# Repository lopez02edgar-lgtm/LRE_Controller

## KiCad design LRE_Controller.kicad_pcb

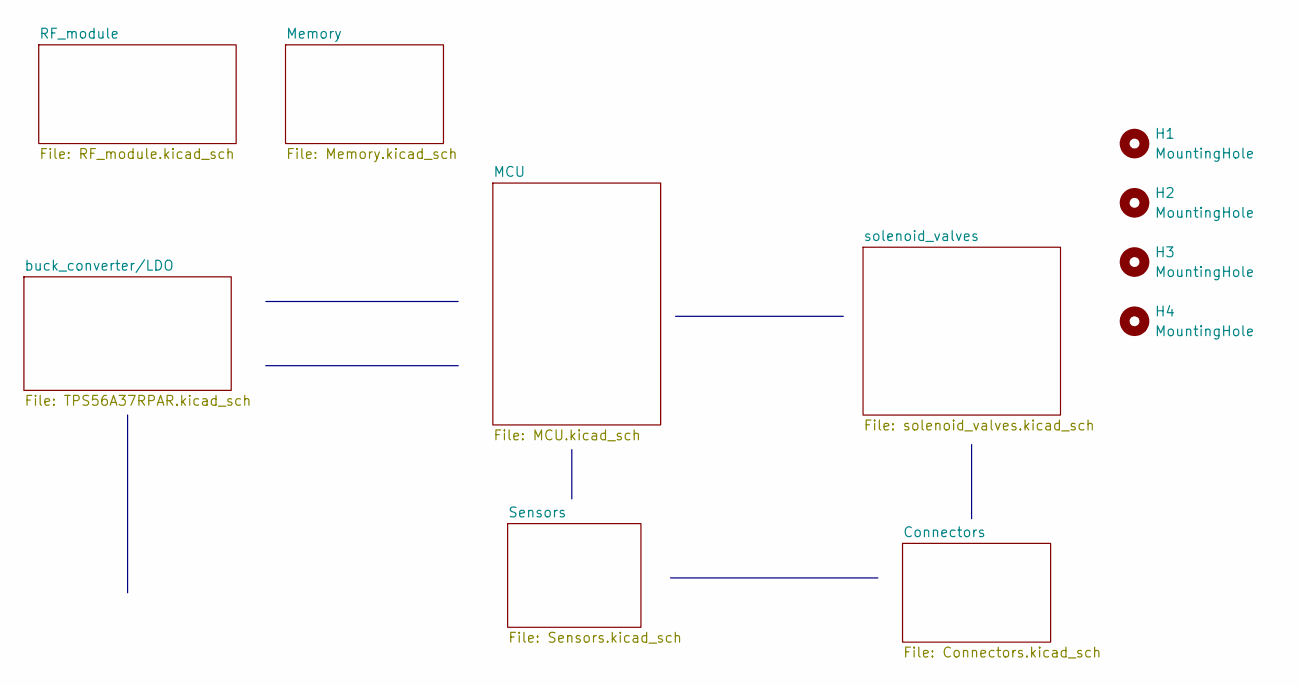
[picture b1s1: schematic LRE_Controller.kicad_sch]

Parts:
H1, H2, H3, H4: MountingHole; MountingHole_3.2mm_M3

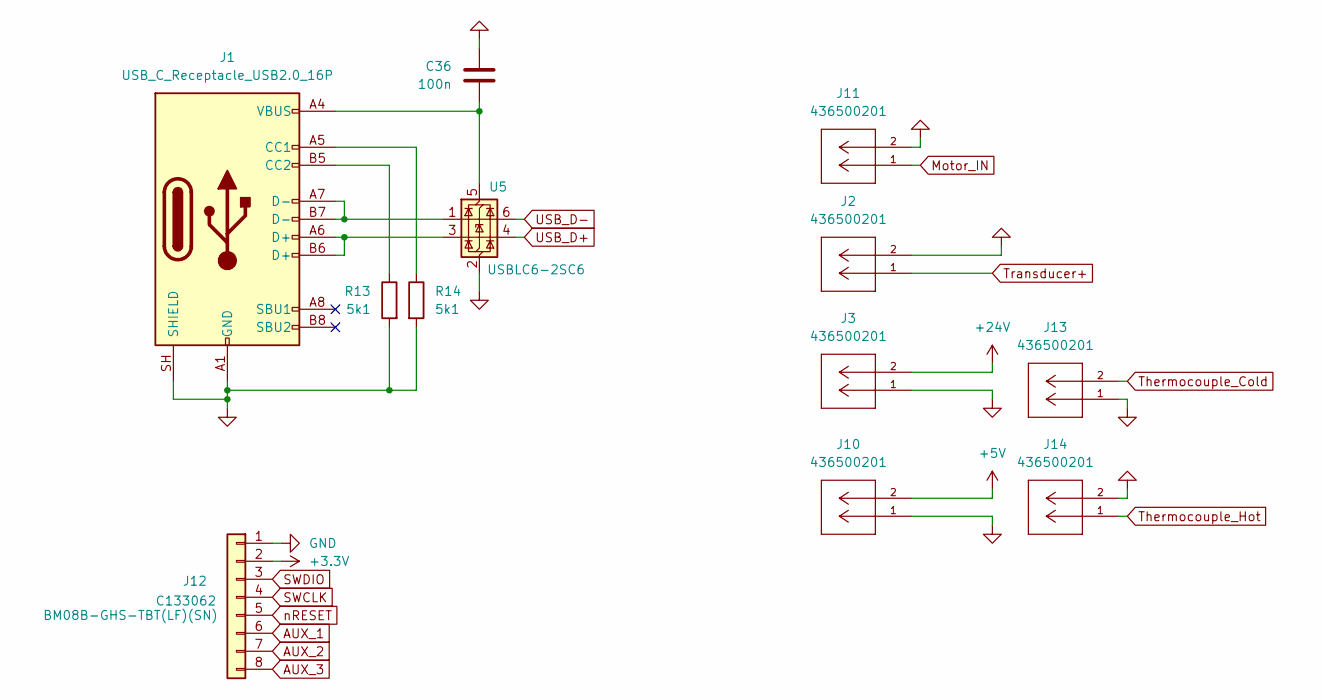
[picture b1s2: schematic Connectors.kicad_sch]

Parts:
C36: 100n; C_0402_1005Metric
J1: USB_C_Receptacle_USB2.0_16P; USB_C_Receptacle_GCT_USB4105-xx-A_16P_TopMnt_Horizontal
J2, J3, J10, J11, J13, J14: 436500201; CONN_SD-43650-001_02_MOL; MANUFACTURER_PART_NUMBER 436500201
J12: BM08B-GHS-TBT(LF)(SN); JST_GH_BM08B-GHS-TBT_1x08-1MP_P1.25mm_Vertical; LCSC C133062
R13, R14: 5k1; R_0402_1005Metric
U5: USBLC6-2SC6; SOT-23-6

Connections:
+3.3V: J12.2; also elsewhere on the board
+5V: J10.2; also elsewhere on the board
+24V: J3.2; also elsewhere on the board
ADC0 (P.T): J2.1; also elsewhere on the board
AUX_1: J12.6; also elsewhere on the board
AUX_2: J12.7; also elsewhere on the board
AUX_3: J12.8; also elsewhere on the board
GND: C36.1, J1.A1 (GND), J1.A12 (GND), J1.B1 (GND), J1.B12 (GND), J1.SH (SHIELD), J2.2, J3.1, J10.1, J11.2, J12.1, J13.1, J14.2, R13.2, R14.2, U5.2 (GND); also elsewhere on the board
Motor_IN: J11.1; also elsewhere on the board
unnamed: J1.A5 (CC1), R14.1
unnamed: J1.B5 (CC2), R13.1
unnamed: J1.A6 (D+), J1.B6 (D+), U5.3 (I/O2)
unnamed: J1.A7 (D-), J1.B7 (D-), U5.1 (I/O1)
unnamed: C36.2, J1.A4 (VBUS), J1.A9 (VBUS), J1.B4 (VBUS), J1.B9 (VBUS), U5.5 (VBUS)
SWCLK: J12.4; also elsewhere on the board
SWDIO: J12.3; also elsewhere on the board
Thermocouple_Cold: J13.2; also elsewhere on the board
Thermocouple_Hot: J14.1; also elsewhere on the board
USB_D+: U5.4 (I/O2); also elsewhere on the board
USB_D-: U5.6 (I/O1); also elsewhere on the board
nRESET: J12.5; also elsewhere on the board

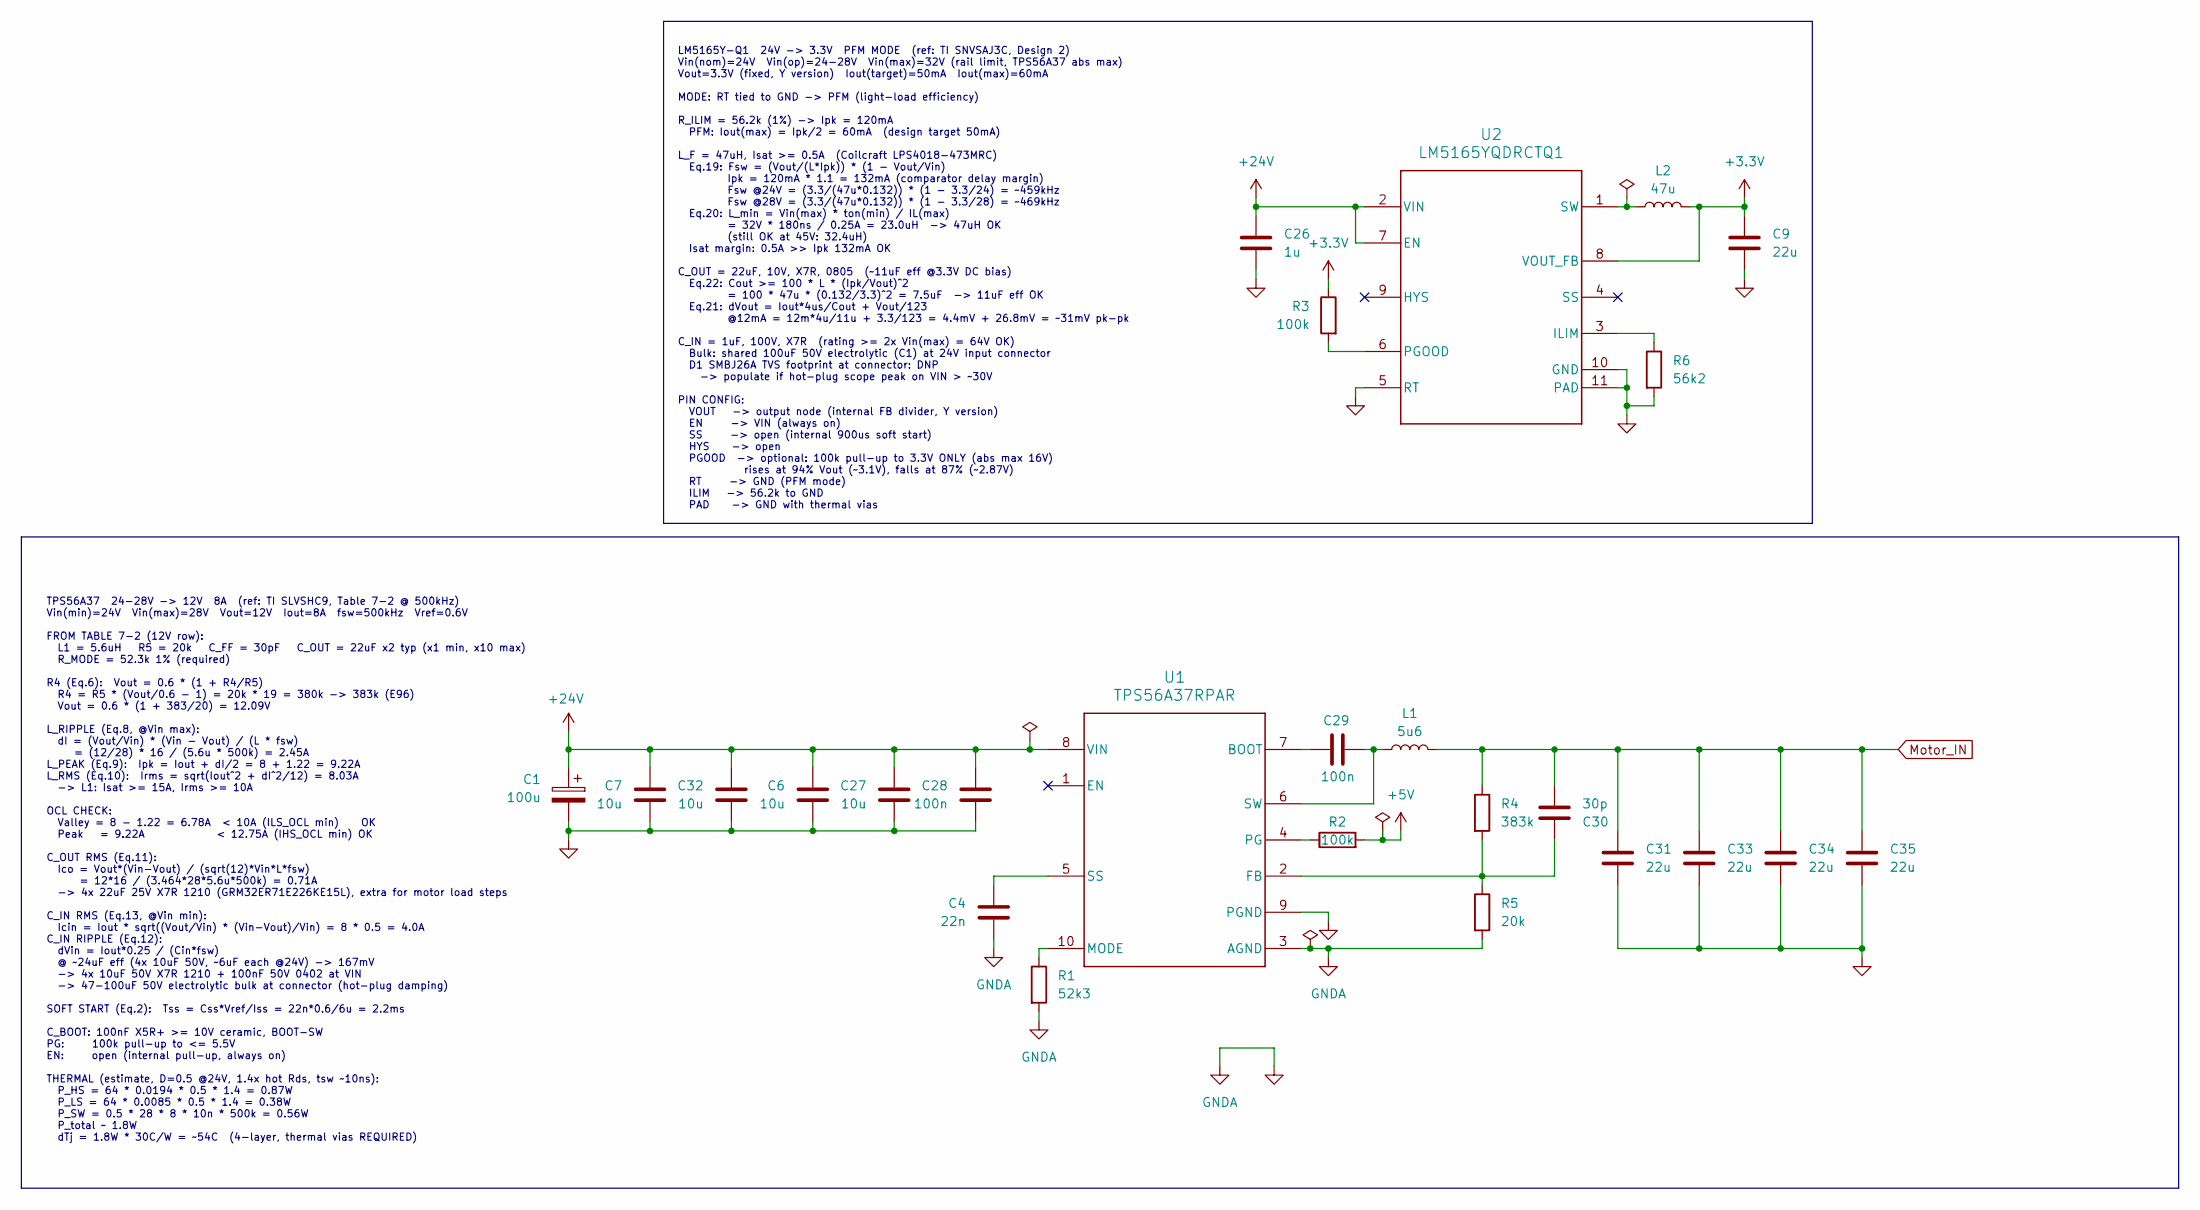
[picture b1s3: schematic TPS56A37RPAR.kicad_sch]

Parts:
C1: 100u; CAP_EEFK_J16_PAN
C4: 22n; C_0402_1005Metric
C6, C7, C27, C32: 10u; C_1210_3225Metric
C9: 22u; C_0402_1005Metric
C26: 1u; C_0805_2012Metric
C28: 100n; C_1210_3225Metric
C29: 100n; C_0805_2012Metric
C30: 30p; C_0402_1005Metric
C31, C33, C34, C35: 22u; C_1210_3225Metric
L1: 5u6; L_Wurth_WE-HCI-1890
L2: 47u; IND_LPS4018-473MRC
R1: 52k3; R_0402_1005Metric
R2, R3: 100k; R_0402_1005Metric
R4: 383k; R_0402_1005Metric
R5: 20k; R_0402_1005Metric
R6: 56k2; R_0402_1005Metric
U1: TPS56A37RPAR; RPA0010A-MFG
U2: LM5165YQDRCTQ1; DRC0010J

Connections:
+3.3V: C9.2, L2.2, R3.1, U2.8 (VOUT_FB); also elsewhere on the board
+5V: R2.2; also elsewhere on the board
+24V: C1.1, C6.2, C7.2, C26.2, C27.2, C28.2, C32.2, U1.8 (VIN), U2.2 (VIN), U2.7 (EN); also elsewhere on the board
GND: C1.2, C4.1, C6.1, C7.1, C9.1, C26.1, C27.1, C28.1, C31.1, C32.1, C33.1, C34.1, C35.1, R1.2, R5.2, R6.2, U1.3 (AGND), U1.9 (PGND), U2.5 (RT), U2.10 (GND), U2.11 (PAD); also elsewhere on the board
Motor_IN: C30.1, C31.2, C33.2, C34.2, C35.2, L1.2, R4.1; also elsewhere on the board
unnamed: C29.2, U1.7 (BOOT)
unnamed: C30.2, R4.2, R5.1, U1.2 (FB)
unnamed: R1.1, U1.10 (MODE)
unnamed: R2.1, U1.4 (PG)
unnamed: C4.2, U1.5 (SS)
unnamed: C29.1, L1.1, U1.6 (SW)
unnamed: R6.1, U2.3 (ILIM)
unnamed: R3.2, U2.6 (PGOOD)
unnamed: L2.1, U2.1 (SW)

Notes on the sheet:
LM5165Y-Q1 24V -> 3.3V PFM MODE (ref: TI SNVSAJ3C, Design 2) Vin(nom)=24V Vin(op)=24-28V Vin(max)=32V (rail limit, TPS56A37 abs max) Vout=3.3V (fixed, Y version) Iout(target)=50mA Iout(max)=60mA MODE: RT tied to GND -> PFM (light-load efficiency) R_ILIM = 56.2k (1%) -> Ipk = 120mA PFM: Iout(max) = 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
TPS56A37 24-28V -> 12V 8A (ref: TI SLVSHC9, Table 7-2 @ 500kHz) Vin(min)=24V Vin(max)=28V Vout=12V Iout=8A fsw=500kHz Vref=0.6V FROM TABLE 7-2 (12V row): L1 = 5.6uH R5 = 20k C_FF = 30pF C_OUT = 22uF x2 typ (x1 min, x10 max) R_MODE = 52.3k 1% (required) R4 (Eq.6): Vout = 0.6 * (1 + R4/R5) R4 = R5 * 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

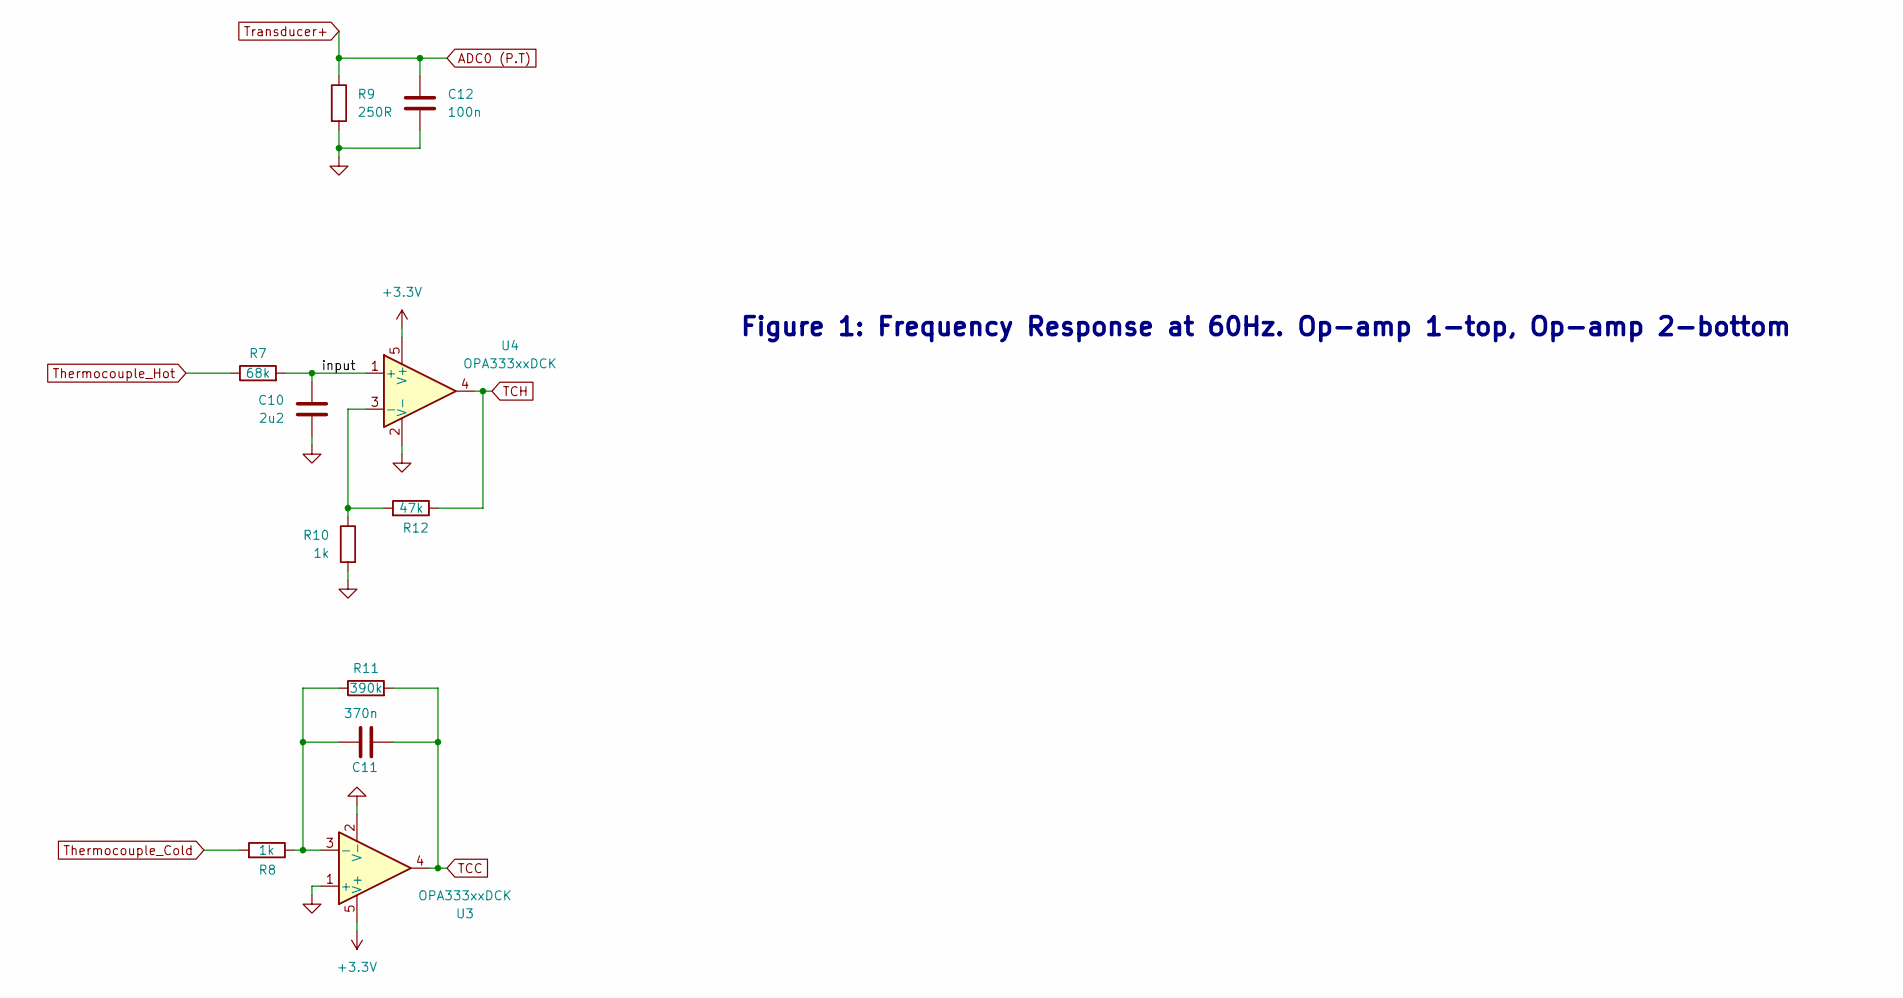
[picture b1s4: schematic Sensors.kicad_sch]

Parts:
C10: 2u2; C_0402_1005Metric
C11: 370n; C_0402_1005Metric
C12: 100n; C_0402_1005Metric
R7: 68k; R_0402_1005Metric
R8, R10: 1k; R_0402_1005Metric
R9: 250R; R_0402_1005Metric
R11: 390k; R_0402_1005Metric
R12: 47k; R_0402_1005Metric
U3, U4: OPA333xxDCK; SOT-353_SC-70-5

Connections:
+3.3V: U3.5 (V+), U4.5 (V+); also elsewhere on the board
/Sensors/input: C10.1, R7.2, U4.1 (+)
ADC0 (P.T): C12.1, R9.1; also elsewhere on the board
GND: C10.2, C12.2, R9.2, R10.2, U3.1 (+), U3.2 (V-), U4.2 (V-); also elsewhere on the board
unnamed: C11.1, R8.1, R11.1, U3.3 (-)
unnamed: R10.1, R12.2, U4.3 (-)
TCC: C11.2, R11.2, U3.4; also elsewhere on the board
TCH: R12.1, U4.4; also elsewhere on the board
Thermocouple_Cold: R8.2; also elsewhere on the board
Thermocouple_Hot: R7.1; also elsewhere on the board

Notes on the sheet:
Figure 1: Frequency Response at 60Hz. Op-amp 1-top, Op-amp 2-bottom

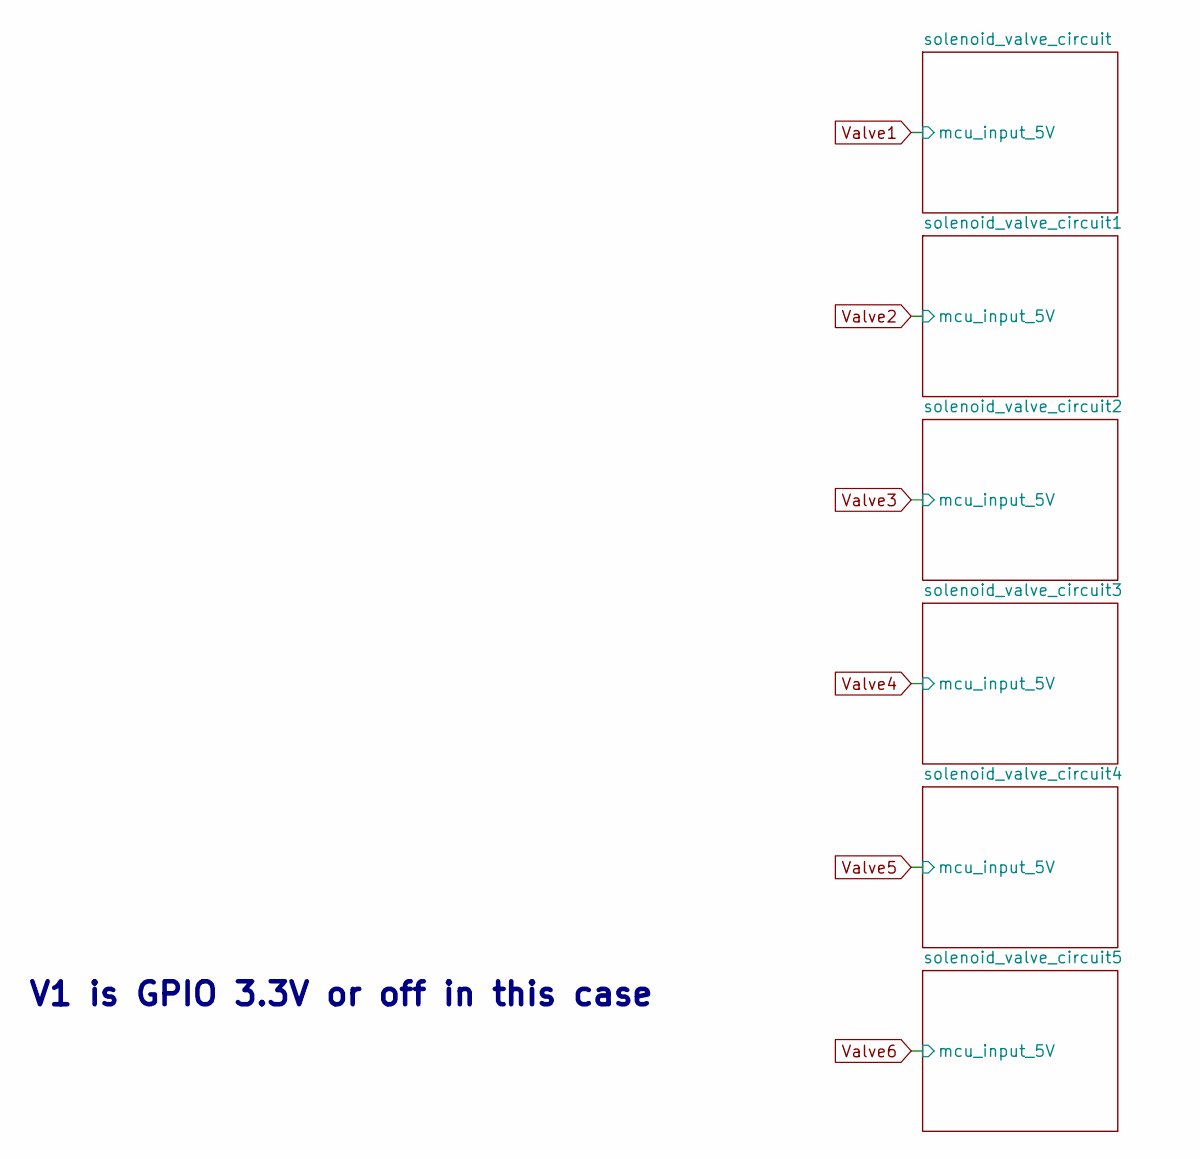
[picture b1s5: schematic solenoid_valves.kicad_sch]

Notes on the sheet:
V1 is GPIO 3.3V or off in this case

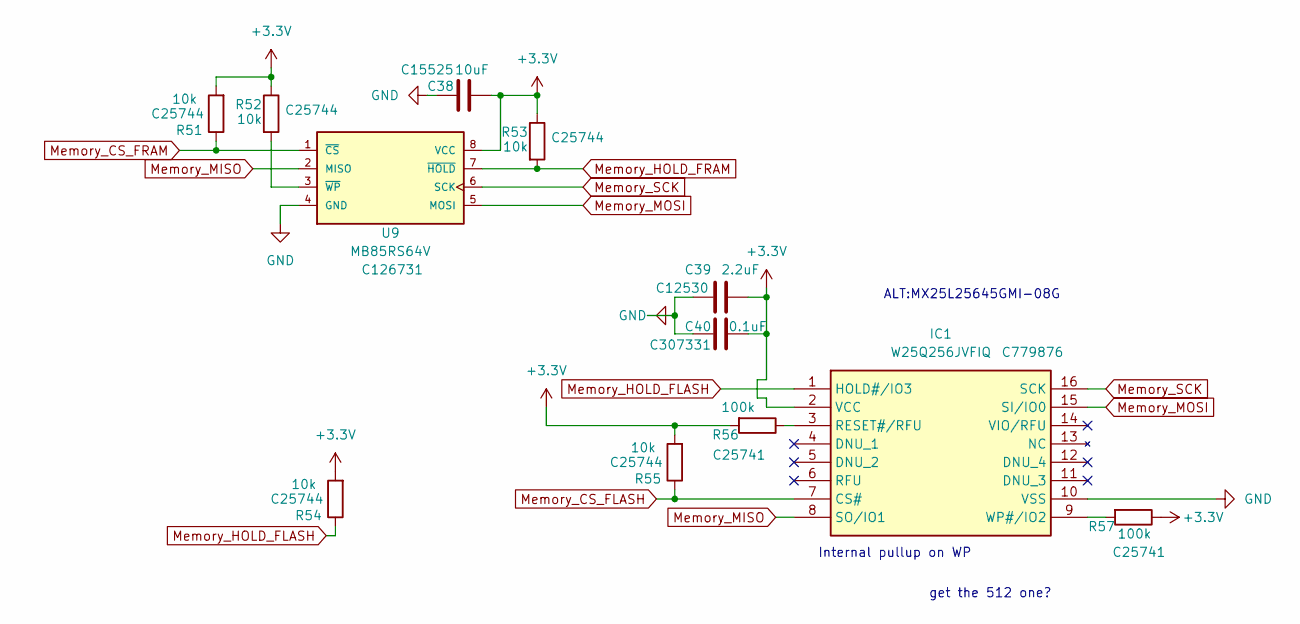
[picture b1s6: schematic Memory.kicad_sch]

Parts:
C38: 10uF; C_0402_1005Metric; LCSC C15525
C39: 2.2uF; C_0402_1005Metric; LCSC C12530
C40: 0.1uF; C_0402_1005Metric; LCSC C307331
IC1: W25Q256JVFIQ; SOIC127P1032X264-16N; Mouser Part Number 727-S25FL512SAGMFV00
R51, R52, R53, R54, R55: 10k; R_0402_1005Metric; LCSC C25744
R56, R57: 100k; R_0402_1005Metric; LCSC C25741
U9: MB85RS64V; SOIC127P600X175-8N; LCSC C126731

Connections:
+3.3V: C38.2, C39.1, C40.1, IC1.2 (VCC), R51.2, R52.1, R53.1, R54.2, R55.2, R56.2, R57.1, U9.8 (VCC); also elsewhere on the board
GND: C38.1, C39.2, C40.2, IC1.10 (VSS), U9.4 (GND); also elsewhere on the board
Memory_CS_FLASH: IC1.7 (CS#), R55.1; also elsewhere on the board
Memory_CS_FRAM: R51.1, U9.1 (~CS); also elsewhere on the board
Memory_HOLD_FLASH: IC1.1 (HOLD#/IO3), R54.1; also elsewhere on the board
Memory_HOLD_FRAM: R53.2, U9.7 (~HOLD); also elsewhere on the board
Memory_MISO: IC1.8 (SO/IO1), U9.2 (MISO); also elsewhere on the board
Memory_MOSI: IC1.15 (SI/IO0), U9.5 (MOSI); also elsewhere on the board
Memory_SCK: IC1.16 (SCK), U9.6 (SCK); also elsewhere on the board
unnamed: IC1.3 (RESET#/RFU), R56.1
unnamed: IC1.9 (WP#/IO2), R57.2
unnamed: R52.2, U9.3 (~WP)

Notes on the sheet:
ALT:MX25L25645GMI-08G
Internal pullup on WP
get the 512 one?

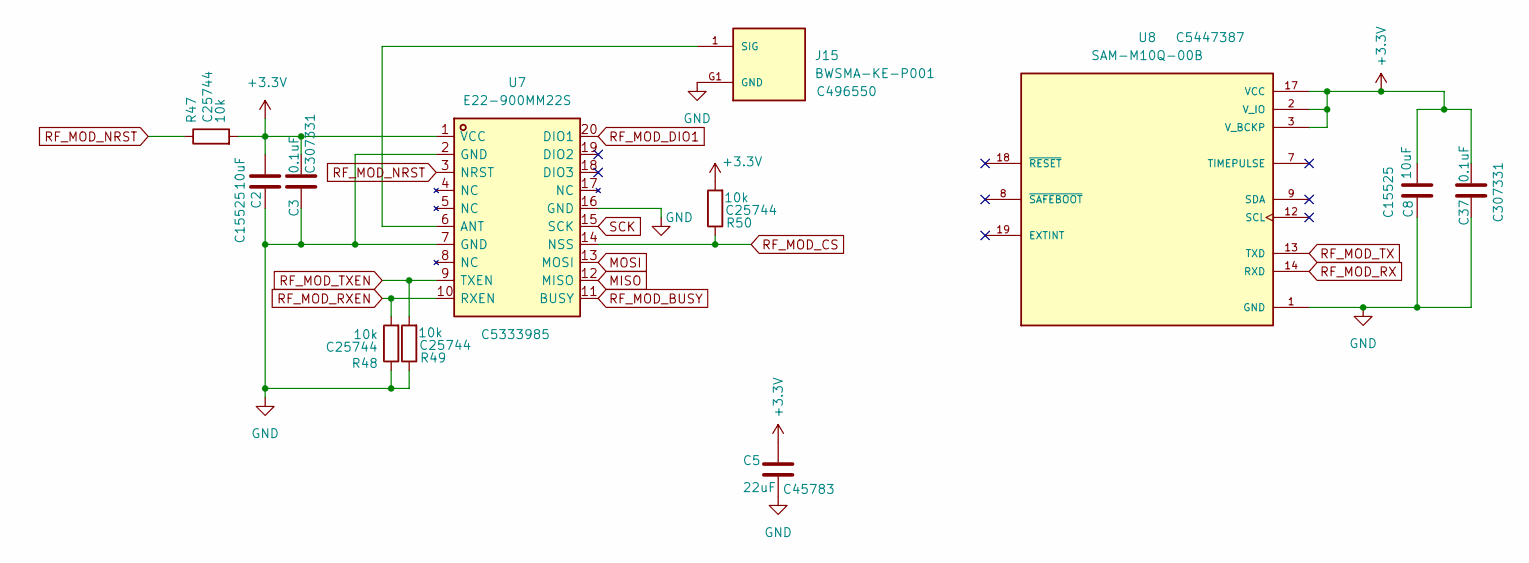
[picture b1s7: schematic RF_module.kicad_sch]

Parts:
C2, C8: 10uF; C_0402_1005Metric; LCSC C15525
C3, C37: 0.1uF; C_0402_1005Metric; LCSC C307331
C5: 22uF; C_0805_2012Metric; LCSC C45783
J15: BWSMA-KE-P001; BATWIRELESS_BWSMA-KE-P001; PARTREV A; LCSC C496550
R47, R48, R49, R50: 10k; R_0402_1005Metric; LCSC C25744
U7: E22-900MM22S; WIRELM-SMD_E22-900M22S; MPN E22-900MM22S; LCSC C5333985
U8: SAM-M10Q-00B; SAMM10Q00B; PARTREV R03; LCSC C5447387

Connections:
+3.3V: C2.2, C3.1, C5.1, C8.2, C37.1, R47.2, R50.2, U7.1 (VCC), U8.2 (V_IO), U8.3 (V_BCKP), U8.17 (VCC); also elsewhere on the board
GND: C2.1, C3.2, C5.2, C8.1, C37.2, J15.G1 (GND), J15.G2 (GND), J15.G3 (GND), J15.G4 (GND), R48.1, R49.1, U7.2 (GND), U7.7 (GND), U7.16 (GND), U8.1 (GND), U8.4 (GND), U8.5 (GND), U8.6 (GND), U8.10 (GND), U8.11 (GND), U8.15 (GND), U8.16 (GND), U8.20 (GND); also elsewhere on the board
MISO: U7.12 (MISO)
MOSI: U7.13 (MOSI)
unnamed: J15.1 (SIG), U7.6 (ANT)
RF_MOD_BUSY: U7.11 (BUSY); also elsewhere on the board
RF_MOD_CS: R50.1, U7.14 (NSS); also elsewhere on the board
RF_MOD_DIO1: U7.20 (DIO1); also elsewhere on the board
RF_MOD_NRST: R47.1, U7.3 (NRST); also elsewhere on the board
RF_MOD_RX: U8.14 (RXD); also elsewhere on the board
RF_MOD_RXEN: R48.2, U7.10 (RXEN); also elsewhere on the board
RF_MOD_TX: U8.13 (TXD); also elsewhere on the board
RF_MOD_TXEN: R49.2, U7.9 (TXEN); also elsewhere on the board
SCK: U7.15 (SCK)

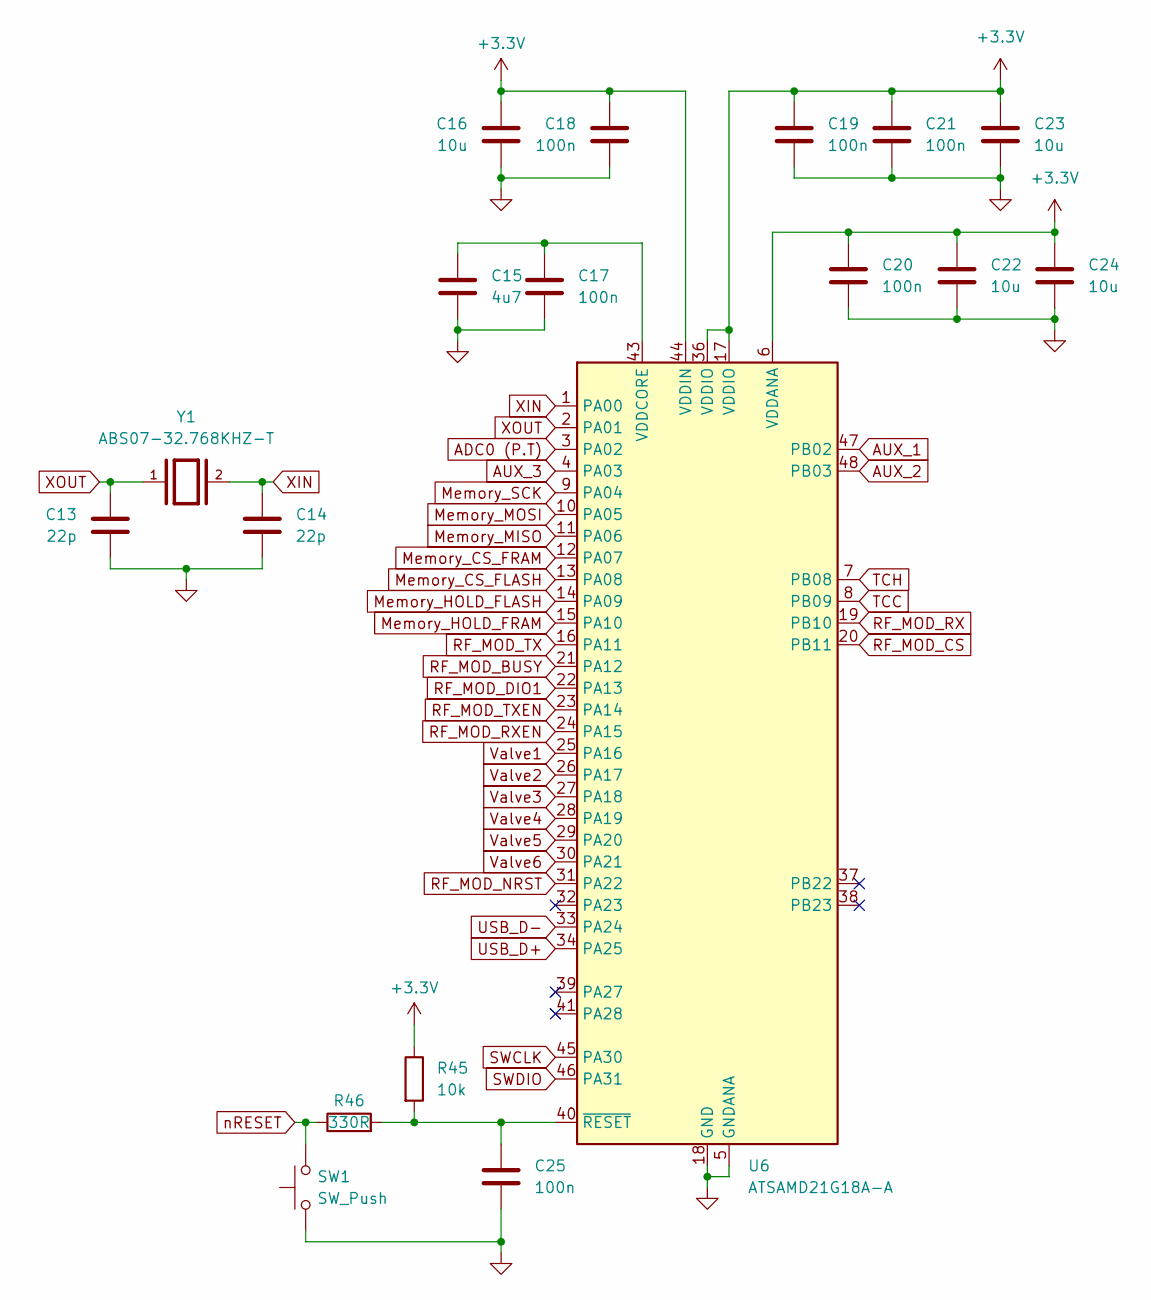
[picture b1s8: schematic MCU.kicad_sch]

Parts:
C13, C14: 22p; C_0402_1005Metric
C15: 4u7; C_0402_1005Metric
C16, C22, C23, C24: 10u; C_0402_1005Metric
C17, C18, C19, C20, C21, C25: 100n; C_0402_1005Metric
R45: 10k; R_0402_1005Metric
R46: 330R; R_0402_1005Metric
SW1: SW_Push; SW_SPST_B3S-1000
U6: ATSAMD21G18A-A; TQFP-48_7x7mm_P0.5mm
Y1: ABS07-32.768KHZ-T; XTAL_ABS07-32.768KHZ-T; PARTREV 08.19.15

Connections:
+3.3V: C16.1, C18.1, C19.1, C20.1, C21.1, C22.1, C23.1, C24.1, R45.1, U6.6 (VDDANA), U6.17 (VDDIO), U6.36 (VDDIO), U6.44 (VDDIN); also elsewhere on the board
ADC0 (P.T): U6.3 (PA02); also elsewhere on the board
AUX_1: U6.47 (PB02); also elsewhere on the board
AUX_2: U6.48 (PB03); also elsewhere on the board
AUX_3: U6.4 (PA03); also elsewhere on the board
GND: C13.2, C14.2, C15.2, C16.2, C17.2, C18.2, C19.2, C20.2, C21.2, C22.2, C23.2, C24.2, C25.2, SW1.1, U6.5 (GNDANA), U6.18 (GND), U6.35 (GND), U6.42 (GND); also elsewhere on the board
Memory_CS_FLASH: U6.13 (PA08); also elsewhere on the board
Memory_CS_FRAM: U6.12 (PA07); also elsewhere on the board
Memory_HOLD_FLASH: U6.14 (PA09); also elsewhere on the board
Memory_HOLD_FRAM: U6.15 (PA10); also elsewhere on the board
Memory_MISO: U6.11 (PA06); also elsewhere on the board
Memory_MOSI: U6.10 (PA05); also elsewhere on the board
Memory_SCK: U6.9 (PA04); also elsewhere on the board
unnamed: C15.1, C17.1, U6.43 (VDDCORE)
unnamed: C25.1, R45.2, R46.2, U6.40 (~RESET)
RF_MOD_BUSY: U6.21 (PA12); also elsewhere on the board
RF_MOD_CS: U6.20 (PB11); also elsewhere on the board
RF_MOD_DIO1: U6.22 (PA13); also elsewhere on the board
RF_MOD_NRST: U6.31 (PA22); also elsewhere on the board
RF_MOD_RX: U6.19 (PB10); also elsewhere on the board
RF_MOD_RXEN: U6.24 (PA15); also elsewhere on the board
RF_MOD_TX: U6.16 (PA11); also elsewhere on the board
RF_MOD_TXEN: U6.23 (PA14); also elsewhere on the board
SWCLK: U6.45 (PA30); also elsewhere on the board
SWDIO: U6.46 (PA31); also elsewhere on the board
TCC: U6.8 (PB09); also elsewhere on the board
TCH: U6.7 (PB08); also elsewhere on the board
USB_D+: U6.34 (PA25); also elsewhere on the board
USB_D-: U6.33 (PA24); also elsewhere on the board
Valve1: U6.25 (PA16); also elsewhere on the board
Valve2: U6.26 (PA17); also elsewhere on the board
Valve3: U6.27 (PA18); also elsewhere on the board
Valve4: U6.28 (PA19); also elsewhere on the board
Valve5: U6.29 (PA20); also elsewhere on the board
Valve6: U6.30 (PA21); also elsewhere on the board
XIN: C14.1, U6.1 (PA00), Y1.2
XOUT: C13.1, U6.2 (PA01), Y1.1
nRESET: R46.1, SW1.2; also elsewhere on the board

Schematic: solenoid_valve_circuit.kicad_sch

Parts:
D1: US1M; D_SMA
J4: 436500201; CONN_SD-43650-001_02_MOL; MANUFACTURER_PART_NUMBER 436500201
Q1: MMBT3904; SOT-23
Q2: NMOS; SOT230P700X185-4N
R15, R16: 10k; R_0402_1005Metric
R17: 4k7; R_0402_1005Metric
R18: 330; R_0402_1005Metric
R19: 100k; R_0402_1005Metric

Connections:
+3.3V: R15.1; also elsewhere on the board
+5V: R17.1; also elsewhere on the board
GND: J4.1, Q1.2 (E), Q2.3 (S), R19.1; also elsewhere on the board
unnamed: D1.1 (K), D1.2 (A), J4.2, Q2.1 (D)
unnamed: Q1.1 (B), R16.2
unnamed: Q1.3 (C), R17.2, R18.1
unnamed: Q2.2 (G), R18.2, R19.2
Valve1: R15.2, R16.1; also elsewhere on the board

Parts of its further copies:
D2, D3, D4, D5, D6: US1M; D_SMA
J5, J6, J7, J8, J9: 436500201; CONN_SD-43650-001_02_MOL; MANUFACTURER_PART_NUMBER 436500201
Q3, Q5, Q7, Q9, Q11: MMBT3904; SOT-23
Q4, Q6, Q8, Q10, Q12: NMOS; SOT230P700X185-4N
R20, R21, R25, R26, R30, R31, R35, R36, R40, R41: 10k; R_0402_1005Metric
R22, R27, R32, R37, R42: 4k7; R_0402_1005Metric
R23, R28, R33, R38, R43: 330; R_0402_1005Metric
R24, R29, R34, R39, R44: 100k; R_0402_1005Metric

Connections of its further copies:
+3.3V: R20.1, R25.1, R30.1, R35.1, R40.1; also elsewhere on the board
+5V: R22.1, R27.1, R32.1, R37.1, R42.1; also elsewhere on the board
GND: J5.1, J6.1, J7.1, J8.1, J9.1, Q3.2 (E), Q4.3 (S), Q5.2 (E), Q6.3 (S), Q7.2 (E), Q8.3 (S), Q9.2 (E), Q10.3 (S), Q11.2 (E), Q12.3 (S), R24.1, R29.1, R34.1, R39.1, R44.1; also elsewhere on the board
unnamed: D2.1 (K), D2.2 (A), J5.2, Q4.1 (D)
unnamed: D3.1 (K), D3.2 (A), J6.2, Q6.1 (D)
unnamed: D4.1 (K), D4.2 (A), J7.2, Q8.1 (D)
unnamed: D5.1 (K), D5.2 (A), J8.2, Q10.1 (D)
unnamed: D6.1 (K), D6.2 (A), J9.2, Q12.1 (D)
unnamed: Q3.1 (B), R21.2
unnamed: Q3.3 (C), R22.2, R23.1
unnamed: Q4.2 (G), R23.2, R24.2
unnamed: Q5.1 (B), R26.2
unnamed: Q5.3 (C), R27.2, R28.1
unnamed: Q6.2 (G), R28.2, R29.2
unnamed: Q7.1 (B), R31.2
unnamed: Q7.3 (C), R32.2, R33.1
unnamed: Q8.2 (G), R33.2, R34.2
unnamed: Q9.1 (B), R36.2
unnamed: Q9.3 (C), R37.2, R38.1
unnamed: Q10.2 (G), R38.2, R39.2
unnamed: Q11.1 (B), R41.2
unnamed: Q11.3 (C), R42.2, R43.1
unnamed: Q12.2 (G), R43.2, R44.2
Valve2: R20.2, R21.1; also elsewhere on the board
Valve3: R25.2, R26.1; also elsewhere on the board
Valve4: R30.2, R31.1; also elsewhere on the board
Valve5: R35.2, R36.1; also elsewhere on the board
Valve6: R40.2, R41.1; also elsewhere on the board

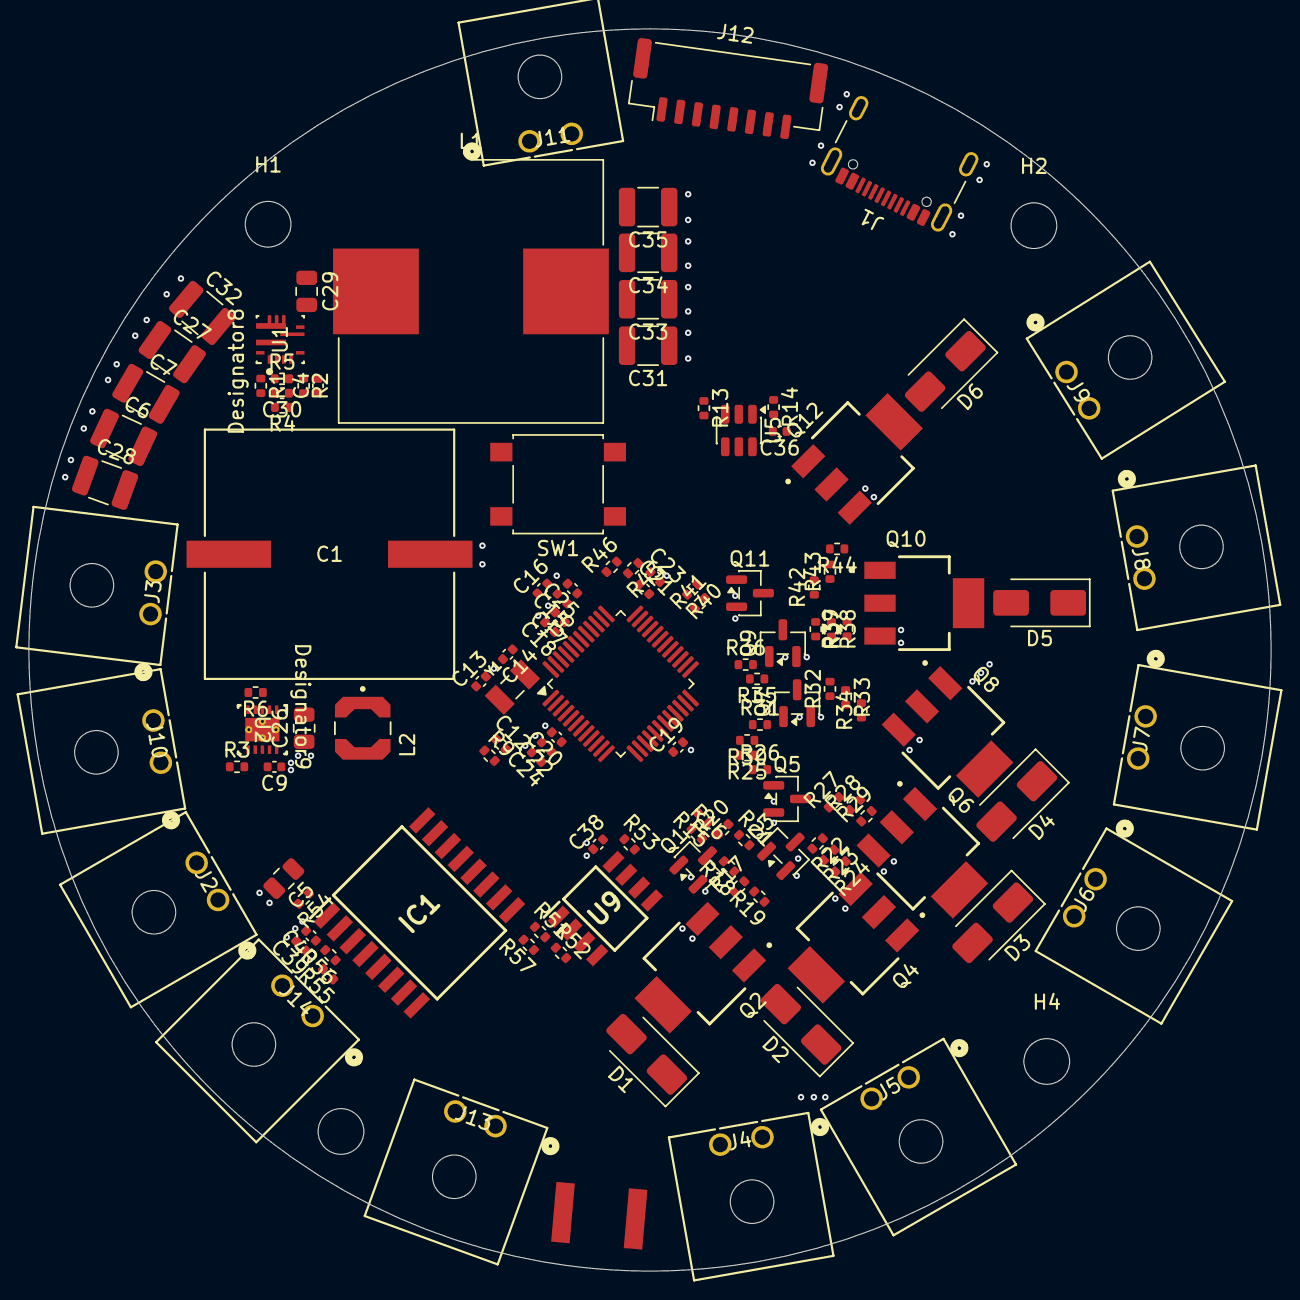
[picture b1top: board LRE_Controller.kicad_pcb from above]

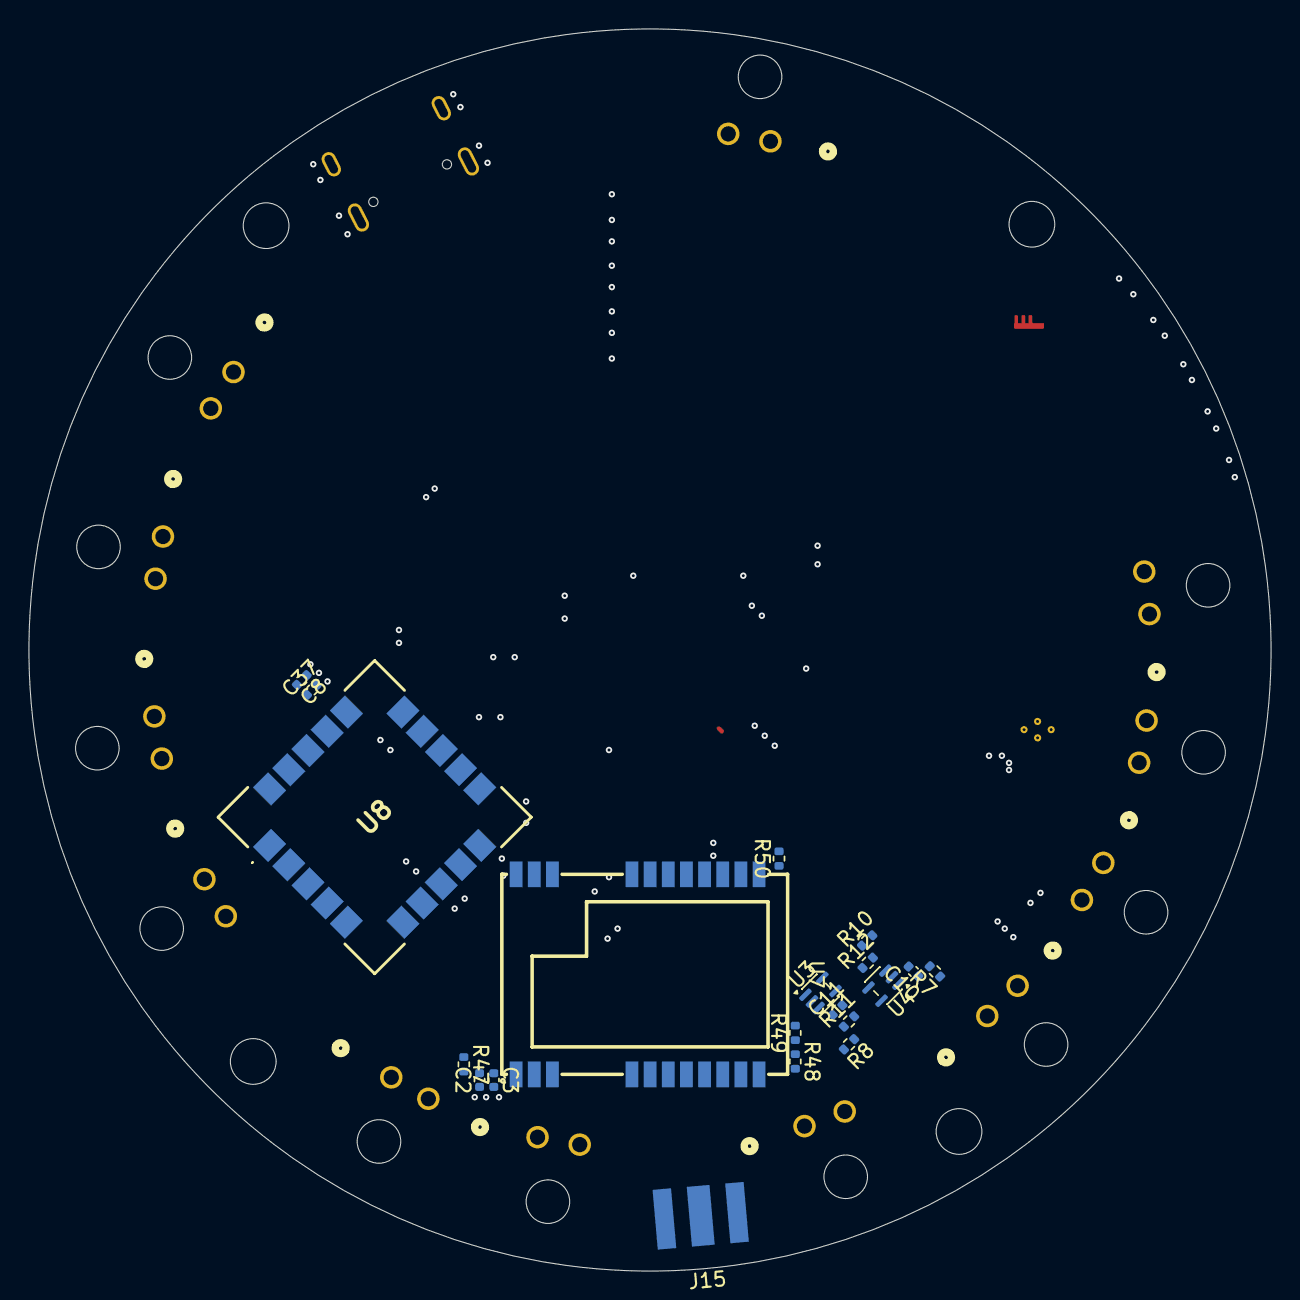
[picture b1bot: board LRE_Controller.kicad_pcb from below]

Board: 4 copper layers, 86.9 x 86.9 mm, 148 parts (20 on the bottom side), 88 nets.
